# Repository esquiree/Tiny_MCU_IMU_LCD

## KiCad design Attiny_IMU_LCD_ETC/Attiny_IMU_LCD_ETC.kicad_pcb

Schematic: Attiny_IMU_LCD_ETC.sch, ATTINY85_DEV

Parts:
C1: C; C_0805
D1, D2: LED; LED_0805
J1: AVR-JTAG-10; Pin_Header_Straight_2x05_Pitch1.27mm
J2: Conn_02X03; Pin_Header_Straight_2x03_Pitch2.54mm
R1, R2, R3: 1k; R_0805
SW1: SW_SPST; Single Dip Siwtch
SW2: SW_SPST; SW_PUSH_6mm
U1: I2C_LCD; SSD1306_NO_BOTTOM_SILK
U2: Bat(1-POS); CR2032 Housing
U3: ATtiny85-20PU; ATtiny85_SMD
U4: LSM6DS3; Bosch_LGA-14_3x2.5mm_Pitch0.5mm

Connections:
+3V3: C1.1, J1.4, J1.7, J2.1, R1.1, R2.1, R3.1, SW1.2, U1.1, U3.8 (VCC), U4.5, U4.8
BTN: J1.3, SW2.1, U3.6 (PB1)
GND: C1.2, D1.1, D2.1, J1.2, J1.10, J2.2, SW2.2, U1.2, U1.5, U2.1, U3.4 (GND), U4.6, U4.7
LED1: D1.2, J2.3, U3.2 (XTAL1/PB3)
LED2: D2.2, J2.5, U3.3 (XTAL2/PB4)
unnamed: SW1.1, U2.2
RST: J1.6, R3.2, U3.1 (~RESET~/PB5)
SCL: J1.1, J2.4, R2.2, U1.3, U3.7 (PB2), U4.14
SDA: J1.9, J2.6, R1.2, U1.4, U3.5 (AREF/PB0), U4.13

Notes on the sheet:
ATTINY85
LEDs &BTN
IMU
LCD
TEST HEADER
BATTERY

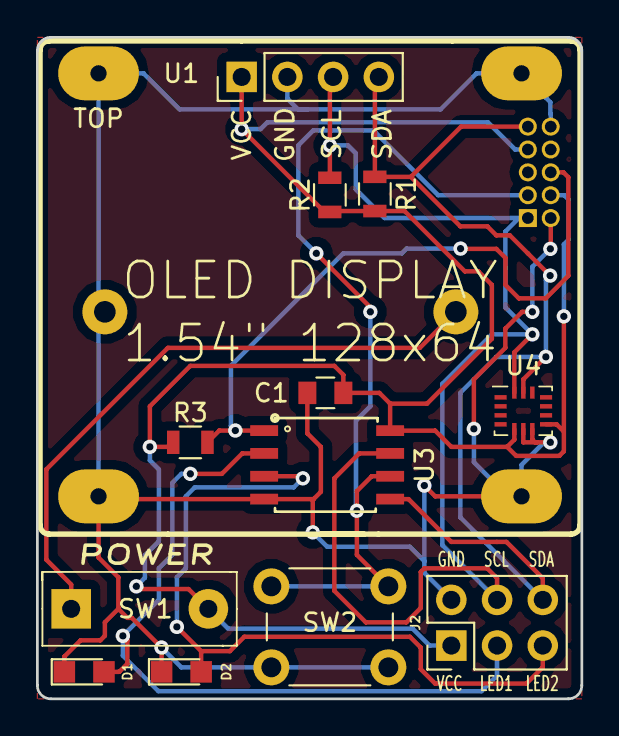
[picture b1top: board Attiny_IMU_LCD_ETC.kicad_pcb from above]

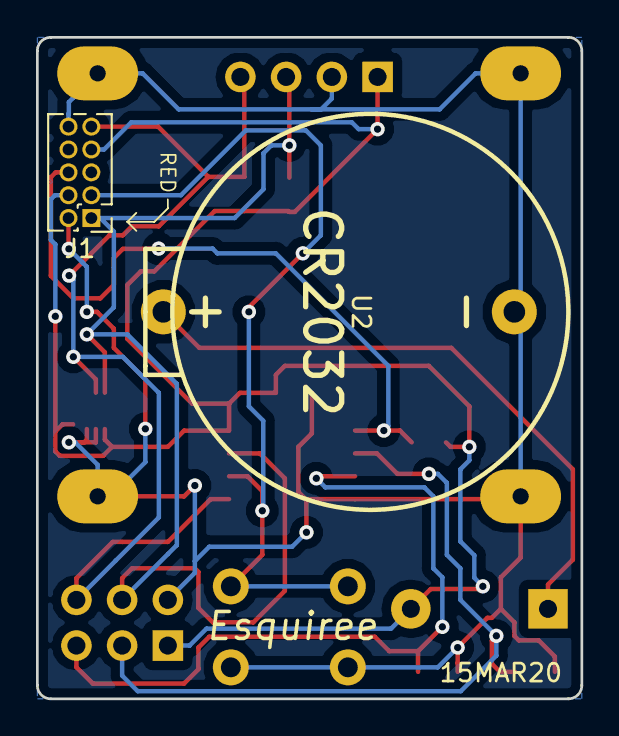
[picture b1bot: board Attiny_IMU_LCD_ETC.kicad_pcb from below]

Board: 2 copper layers, 30.2 x 36.8 mm, 14 parts (2 on the bottom side), 9 nets.
